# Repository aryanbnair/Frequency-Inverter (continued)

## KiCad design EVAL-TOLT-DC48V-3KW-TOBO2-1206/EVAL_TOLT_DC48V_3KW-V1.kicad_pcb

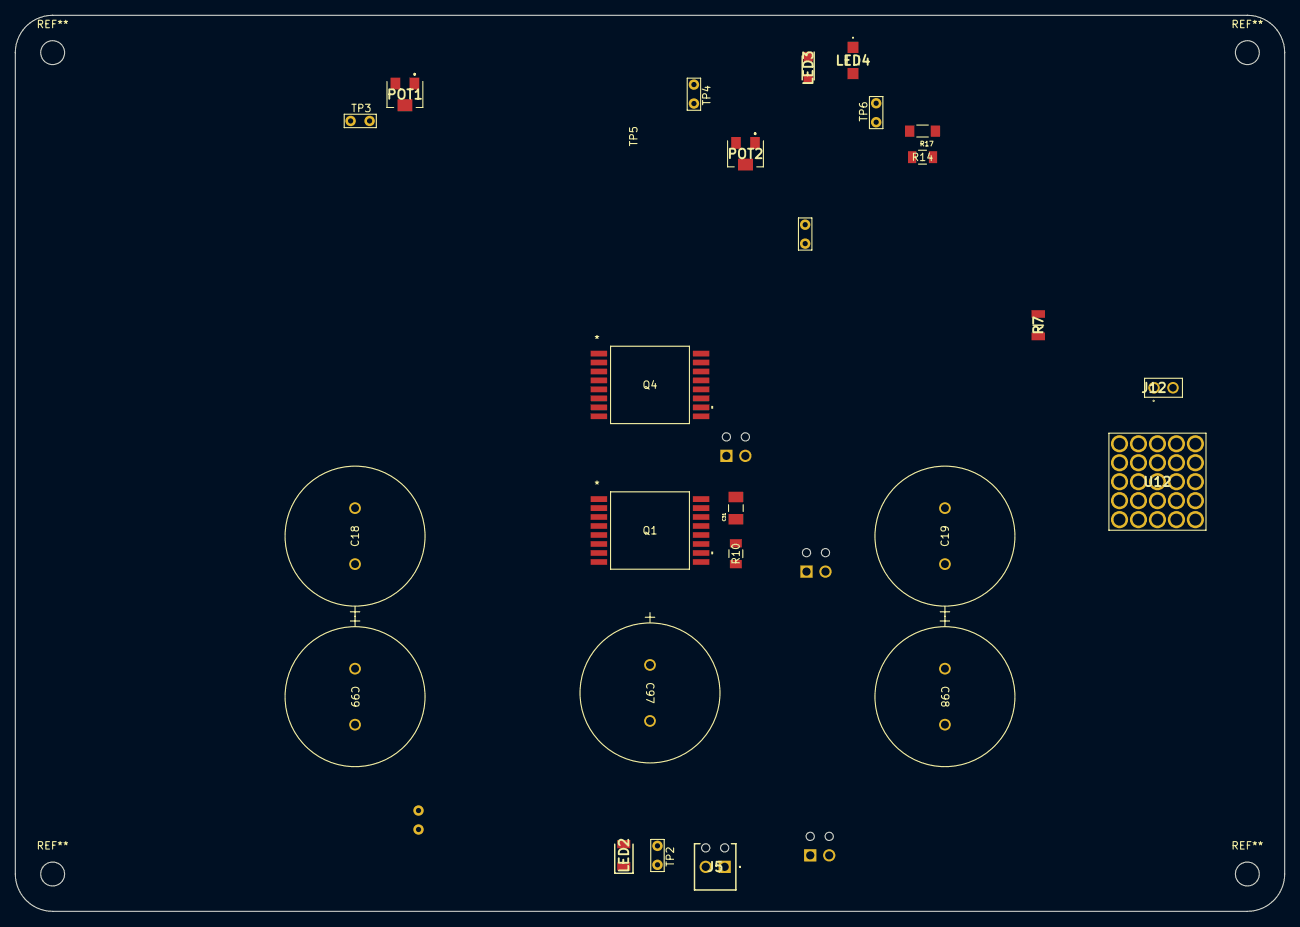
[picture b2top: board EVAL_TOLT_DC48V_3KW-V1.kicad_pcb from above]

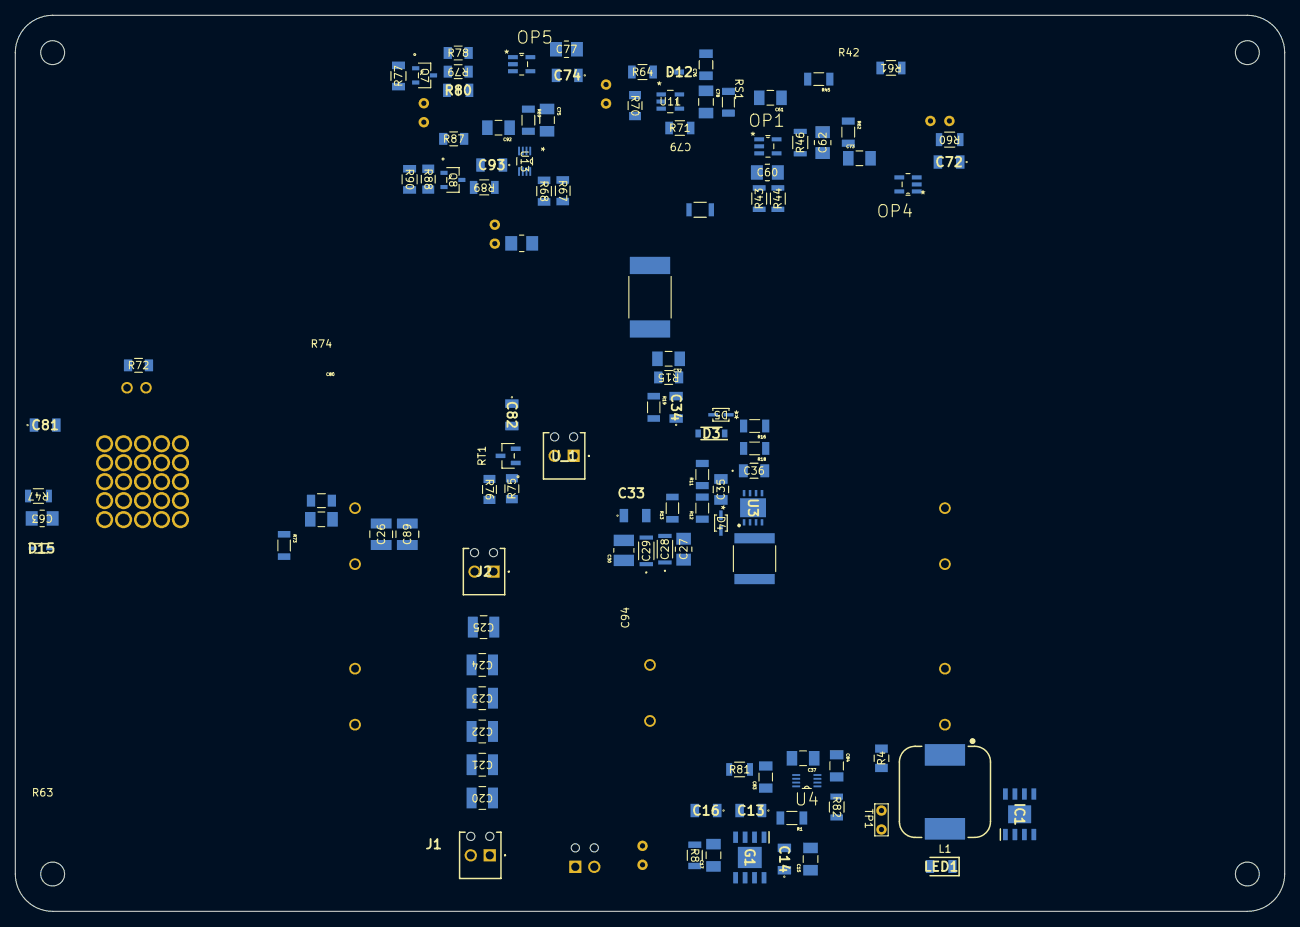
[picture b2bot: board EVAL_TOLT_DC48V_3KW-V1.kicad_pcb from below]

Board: 4 copper layers, 170.0 x 120.0 mm, 133 parts (108 on the bottom side), 60 nets, no tracks yet.

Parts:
C13: 0.01uF 25V 1206; C13
C14, C16: 10uF 25V 0805; C14
C15, C17, C61, C73, C75, C78, C92: 0.1uF 25V 0603; C15
C18, C19, C97, C98, C99: 100nF 50V 0603; C18
C20, C21, C22, C23, C24, C25, C26, C89: 100nF 50V 0603; C20
C27: C1206X104K1RACTU; C1
C28, C29: 2.2uF 100V 1206; C28
C30: 10uF 100V 1210; C30
C31, C32: 10nF 0603 100V; C31
C33, C34: opt/0603/25V; C13
C35: 0.1uF 50V 1206; C35
C36: 10uF 25V 0603; C36
C37: 0.1 uF 25V 0603; C15
C60, C62, C63, C77, C79: 100pF 25V 0603; C8
C72, C74, C93: 1uF 25V 0603; C72
C76: 1nF 25V 0603; C76
C80: C1206X104M3RECAUTO; C15
C81, C82: C1206C105K3RACTM; C72
C83, C84: 100pf 25V 0402; C83
C94: 4.7uF 100V 2220; C94
D3: SMD2150PL-TP; D3
D4, D5: BAT165E63227HTSAI; D4
D12: 500mA/30V/TSLP-2-17; D12
D15: DIODE ZENER; D15
G1: TLS205B0EJ 50V; G1
IC1: LM5013QDDARQ1; DC
J1: V_BAT+; J4
J2: V_BAT-; J4
J5: +5V_EXT; J4
J12: Direction Switch; J12
L1: 33 uH; L1
LED1, LED2: LED GREEN CLEAR 0603; LED1
LED3: LED GREEN CLEAR 0603; LED1-4
LED4: LED RED CLEAR 1206; LED4
OP1, OP4, OP5: AD8615AUJZ; AD8615
POT1, POT2: 50K POT; POT2
Q1, Q4: IAUS300N10S5N015TATMA1; Q1
Q7, Q8: IRLML6346; IRLML6346TRPBF
R1: 0 0805; R1
R4: 1k 0805; R4
R7: 1k 0603; R7
R8: 680 0603; R8
R10, R15: 1.2 0603; R10
R11, R16: 30 0603; R11
R12, R18, R45, R62, R69: 10 0603; R12
R13, R19, R73: 100k 0603; R13
R14: 130k 0603; R14
R17: 5.1k 0603; R17
R42, R46: 12k 0603; R42
R43, R44: 1k 0603; R43
R47, R81, R82: 10 0402; R47
R60: 22k 0603; R60
R61, R67, R68, R71: 1k 0603; R61
R63: 10k 0402; R63
R64: 0 0402; R64
R70: 1M 1206; R70
R72, R78, R79, R87, R88: 10k 0603; R72
R74: 7.87k 0603; R74
R75: 200 0603; R75
R76: 100 0603; R76
R77: 330 0603; R77
R80: 0 0603; R7
R89: 20k 0603; R89
R90: 330; R77
RS1: 1mOhm 1% 5W; HCS3920FT1L00
RT1: MCP9700Ax-ETT; MCP9700AT_E_TT
TP1: 12V; TestPoint_Bridge_Pitch2.54mm_Drill0.7mm
TP2: 5V; TestPoint_Bridge_Pitch2.54mm_Drill0.7mm
TP3: OFFSET; TestPoint_Bridge_Pitch2.54mm_Drill0.7mm
TP4: VREF_OCP; TestPoint_Bridge_Pitch2.54mm_Drill0.7mm
TP5: OCP; TestPoint_Bridge_Pitch2.54mm_Drill0.7mm
TP6: SD; TestPoint_Bridge_Pitch2.54mm_Drill0.7mm
U3: 2EDL8x24G; U3
U4: NL27WZ08USG; U4
U11: LMV331; LMV331M5
U12: PCN10C-32S-2.54DS(72); U12
U13: SN74LVC2G74DCUR; SN74LVC2G74MDCUTEP
U_1: Phase-U; J4

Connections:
5V: C16.2, C17.2, G1.2 (SENSE), J5.2, R1.2, R8.2, TP2.1
12V: C14.2, C15.2, G1.5 (EN), G1.8 (I), L1.2, R4.2, TP1.1
+5V: C78.1, C92.1, LED3.2 (A), R45.1, R60.1, R62.1, R67.1, R69.1, R71.1, R72.1, R75.2, R78.2, R79.2, R87.1, R89.1, U11.5 (V+), U13.2 (D), U13.7 (~PRE), U13.8 (VCC)
+BATT: C27.2, C28.1, C29.1, C30.1, C94.1, Q1.9 (DRAIN), Q1.10 (DRAIN), Q1.11 (DRAIN), Q1.12 (DRAIN), Q1.13 (DRAIN), Q1.14 (DRAIN), Q1.15 (DRAIN), Q1.16 (DRAIN), R10.2, R73.1
/Power Board Connector/DR_EN: Q7.1 (G), R77.1, R78.1
/U-Phase/12V: C36.1, D3.2 (A), U3.1 (VDD)
/U-Phase/+5V: C37.1, U4.8 (VCC)
/U-Phase/U: C31.2, C33.2, C35.2, Q1.1 (SOURCE), Q1.2 (SOURCE), Q1.3 (SOURCE), Q1.4 (SOURCE), Q1.5 (SOURCE), Q1.6 (SOURCE), Q1.7 (SOURCE), Q4.9 (DRAIN), Q4.10 (DRAIN), Q4.11 (DRAIN), Q4.12 (DRAIN), Q4.13 (DRAIN), Q4.14 (DRAIN), Q4.15 (DRAIN), Q4.16 (DRAIN), R13.1, R14.2, R15.2, U3.4 (HS), U_1.1
/U-Phase/U-HI: U3.5 (HI), U4.7 (Y1)
/U-Phase/U-HIN: C83.1, R81.2, U4.1 (A1)
/U-Phase/U-HO: R11.1, R12.1, U3.3 (HO)
/U-Phase/U-LI: U3.6 (LI), U4.3 (Y2)
/U-Phase/U-LIN: C84.1, R82.2, U4.6 (B2)
/U-Phase/U-LO: R16.1, R18.1, U3.8 (LO)
/U-Phase/U_CS+: C32.2, C34.2, C94.2, Q4.1 (SOURCE), Q4.2 (SOURCE), Q4.3 (SOURCE), Q4.4 (SOURCE), Q4.5 (SOURCE), Q4.6 (SOURCE), Q4.7 (SOURCE), R19.1, RS1.2, U3.7 (VSS), U3.9 (VSS)
BEMF_PHASE_U: R14.1, R17.2
GND: C37.2, C61.2, C63.2, C72.2, C73.2, C74.2, C75.2, C76.2, C77.2, C78.2, C79.2, C83.2, C84.2, C92.2, C93.2, D15.2 (A), LED4.1 (K), OP1.2 (V-), OP4.2 (V-), OP5.2 (V-), Q8.2 (S), R7.2, R61.2, R68.2, R88.2, U4.4 (GND), U11.2 (V-), U13.4 (GND)
GNDS: C14.1, C15.1, C16.1, C17.1, C81.1, C82.1, G1.6 (GND), G1.9 (EP), J5.1, LED2.1 (K), Q7.2 (S), RT1.3 (GND)
I_SNS_PHASE_U: C63.1, R47.2
unnamed: C31.1, R10.1
unnamed: C32.1, R15.1
unnamed: C35.1, D3.1 (K), U3.2 (HB)
unnamed: C33.1, D4.2 (A), Q1.8 (GATE), R11.2, R13.2
unnamed: D4.1 (K), R12.2
unnamed: C34.1, D5.2 (A), Q4.8 (GATE), R16.2, R19.2
unnamed: D5.1 (K), R18.2
unnamed: D12.2 (A), R64.2
unnamed: C76.1, D12.1 (K), R63.2, R70.1, U11.1 (+)
unnamed: C80.2, D15.1 (K), R73.2, R74.1
unnamed: C13.2, G1.4 (BYP)
unnamed: C13.1, G1.1 (Q), R1.1
unnamed: IC1.8 (SW), L1.1
unnamed: C18.1, C19.1, C20.1, C21.1, C22.1, C23.1, C24.1, C25.1, C26.1, C89.1, C97.1, C98.1, C99.1, J1.1
unnamed: LED1.2 (A), R4.1
unnamed: LED2.2 (A), R8.1
unnamed: LED3.1 (K), R77.2
unnamed: LED4.2 (A), R90.2
unnamed: C60.1, OP1.3 (+IN), R42.2, R43.2
unnamed: C60.2, C62.2, OP1.4 (-IN), R44.2, R46.1
unnamed: C62.1, OP1.1 (OUT), R46.2, R47.1
unnamed: C61.1, OP1.5 (V+), R45.2
unnamed: C72.1, OP4.3 (+IN), POT1.1, R60.2
unnamed: C73.1, OP4.5 (V+), R62.2
unnamed: C74.1, OP5.3 (+IN), POT2.1, R67.2
unnamed: C77.1, OP5.1 (OUT), OP5.4 (-IN), TP4.1, U11.3 (-)
unnamed: C75.1, OP5.5 (V+), R69.2
unnamed: POT1.2, POT1.3, R61.1
unnamed: POT2.2, POT2.3, R68.1
unnamed: Q7.3 (D), R79.1, R80.2
unnamed: Q8.1 (G), R88.1, R90.1, U13.5 (Q)
unnamed: C82.2, R75.1, RT1.1 (V_{DD})
unnamed: R76.2, RT1.2 (V_{OUT})
unnamed: C81.2, R76.1
unnamed: C79.1, R70.2, R71.2, TP5.1, U11.4, U13.1 (CLK)
unnamed: C93.1, R89.2, U13.6 (~CLR)
OFFSET: OP4.1 (OUT), OP4.4 (-IN), R42.1, R63.1, TP3.1
SD: Q8.3 (D), R80.1, R87.2, TP6.1, U4.2 (B1), U4.5 (A2)
U-L: R81.1, R82.1
V_BAT+: IC1.2 (VIN), IC1.3 (EN/UVLO)
V_BAT-: C18.2, C19.2, C20.2, C21.2, C22.2, C23.2, C24.2, C25.2, C26.2, C27.1, C28.2, C29.2, C30.2, C36.2, C80.1, C89.2, C97.2, C98.2, C99.2, IC1.1 (GND), IC1.9 (EP), J2.1, LED1.1 (K), R7.1, R17.1, R44.1, R74.2, RS1.1

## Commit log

2024-05-27 Original Files by Infineon
    These files were found on Infineon's Website : https://www.infineon.com/cms/en/product/evaluation-boards/eval_tolt_dc48v_3kw/
2024-05-27 3 Phase to Single Phase Modifications
    Changed that were made to the Reference Board to make it a Single Phase Frequency Inverter from a 3 Phase.
2024-05-27 Change 1
    Changed DC-DC Buck Converter and U Phase
2024-05-27 Change 2
2024-05-27 Change 3
2024-05-27 Footprints and Symbols
    Added Footprints from Digikey and other additional symbols and Footprints
2024-05-27 Change 3
    Added More Symbols and Footprints
2024-05-27 Change 4
2024-05-27 Update .gitattributes
    Ignore HTML
2024-05-27 Change 5
2024-05-28 Change 6
2024-10-03 Commit 1
2024-10-10 Added 1206 Config
2024-10-10 1206 Added
    Added New Symbols and Footprints for Capacitors ( 1206 )
2024-10-17 Oct17
2024-10-30 Major Updates v30102024
    Munich Commit
2024-10-30 v30102024
2024-10-30 v30102024v2
2024-10-30 v30102024-3
2024-11-01 v01112024
    New PCB Version for Zones
2024-11-06 v06112024
2024-11-07 v07112024
2024-11-08 v08112024
2024-11-08 v08112024
    Added Heatsink Mounting Holes
2024-11-10 v10112024
2024-11-10 v10112024-2
2024-11-11 v11112024
2024-11-11 v11112024-2
2024-11-11 v11112024-3
2024-11-15 v15112024
2024-11-15 v15112024-3
2024-11-16 v16112024
